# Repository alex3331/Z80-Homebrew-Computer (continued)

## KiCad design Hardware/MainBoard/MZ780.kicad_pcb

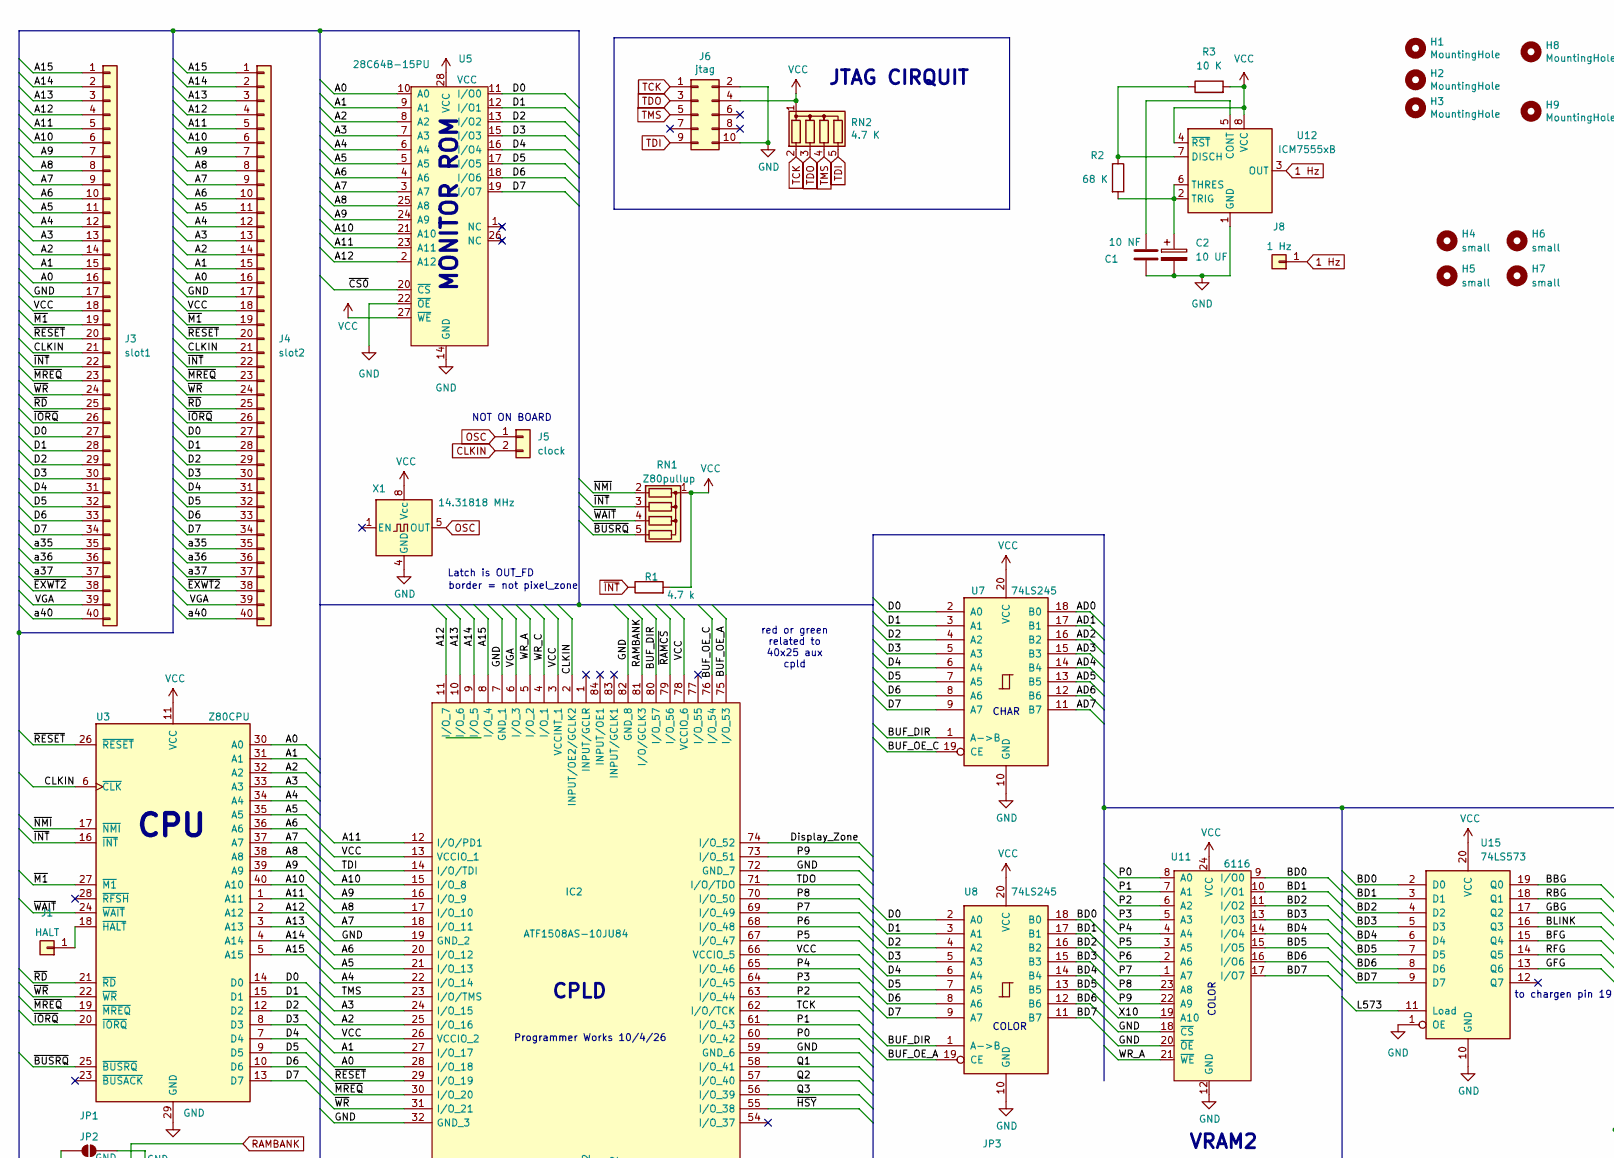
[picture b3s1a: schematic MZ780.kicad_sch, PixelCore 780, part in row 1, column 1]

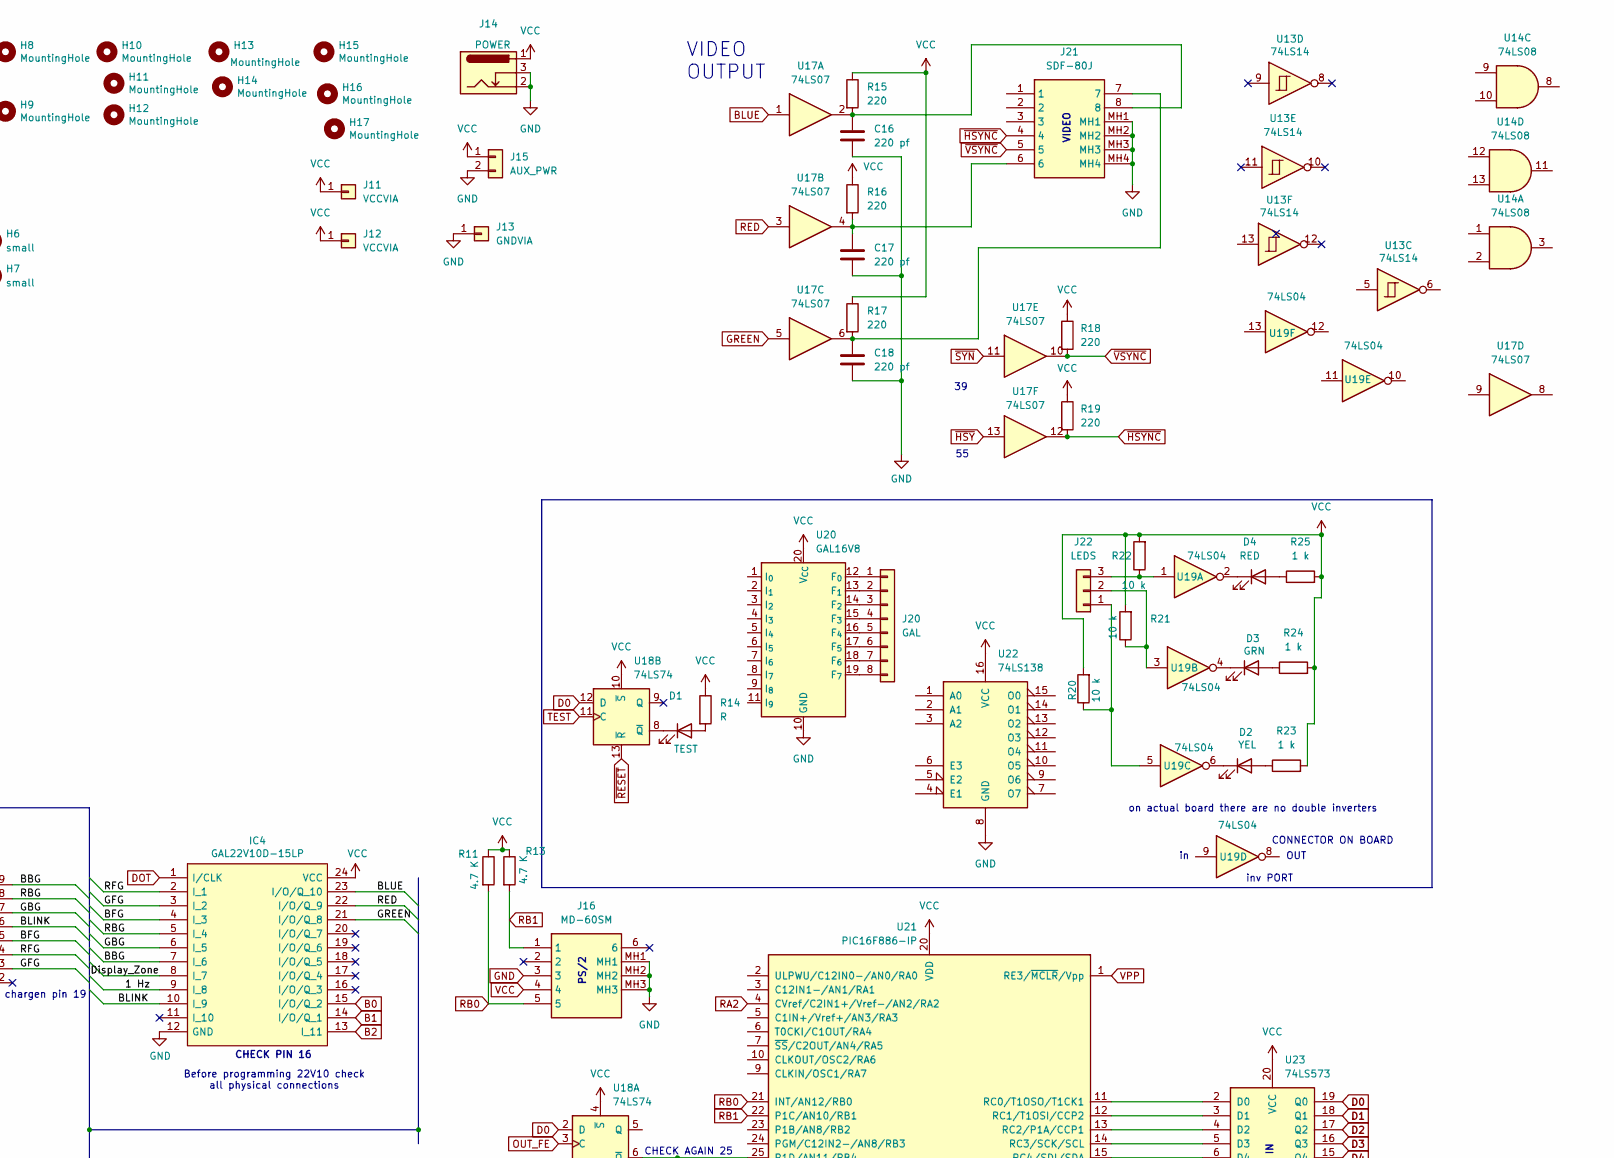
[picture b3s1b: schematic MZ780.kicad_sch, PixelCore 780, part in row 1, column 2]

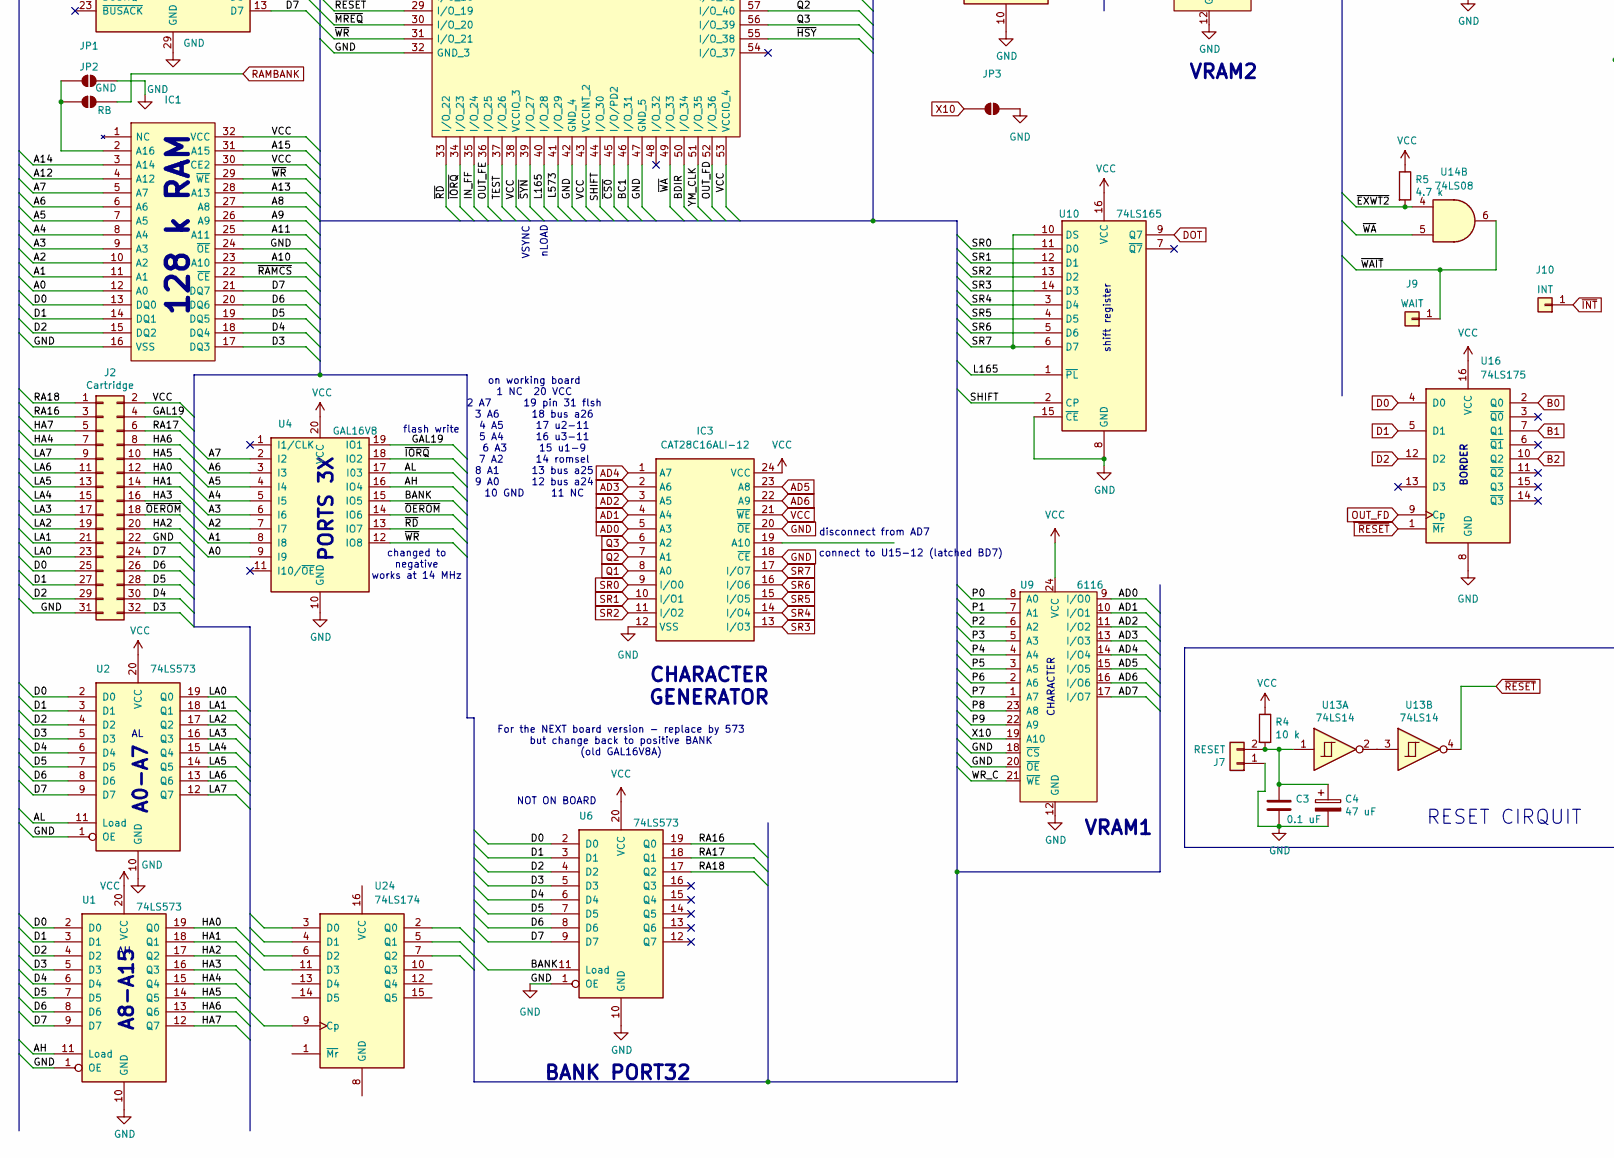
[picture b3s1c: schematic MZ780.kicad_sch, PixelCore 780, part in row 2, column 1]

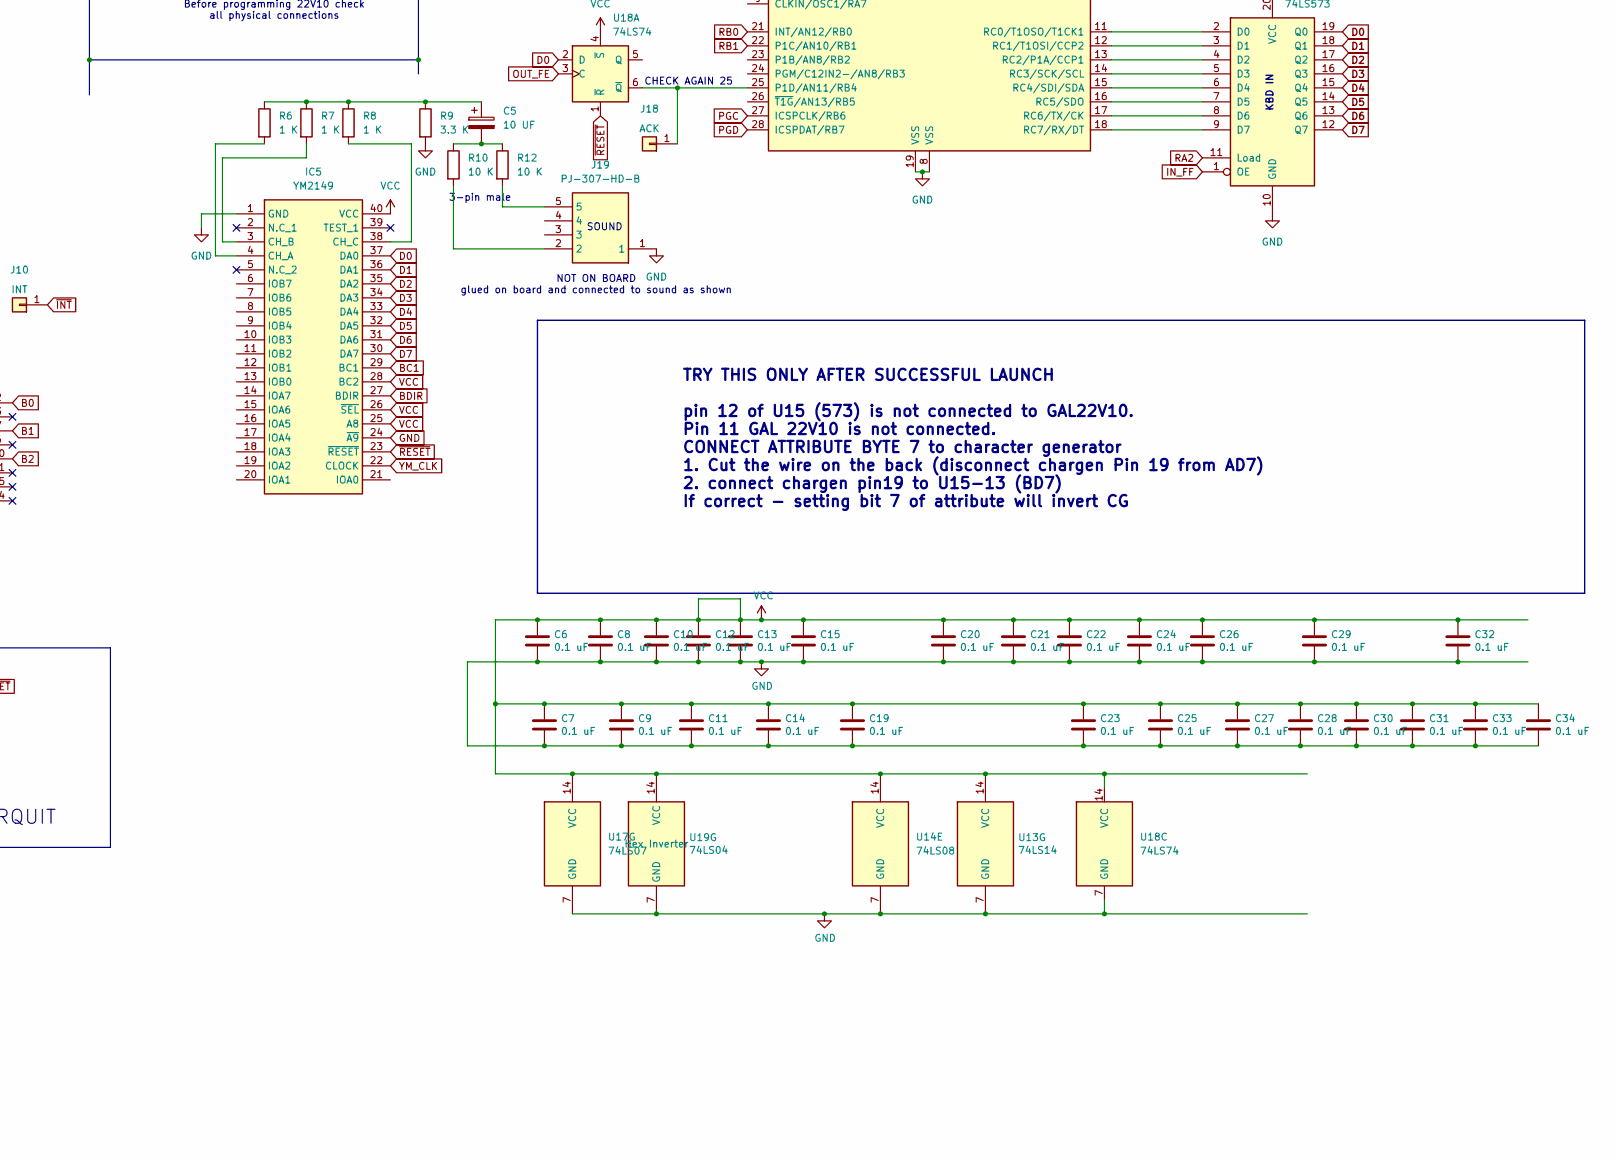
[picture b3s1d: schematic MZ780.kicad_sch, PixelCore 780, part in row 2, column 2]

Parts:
C1: 10 NF; C_Disc_D3.0mm_W1.6mm_P2.50mm
C2, C5: 10 UF; CP_Radial_D5.0mm_P2.50mm
C3, C6, C7, C8, C9, C10, C11, C12, C13, C14, C15, C19, C20, C21, C22, C23, C24, C25, C26, C27, C28, C29, C30, C31, C32, C33, C34: 0.1 uF; C_Disc_D3.0mm_W1.6mm_P2.50mm
C4: 47 uF; CP_Radial_D5.0mm_P2.50mm
C16, C17, C18: 220 pf; C_Disc_D3.0mm_W1.6mm_P2.50mm
D1: TEST; LED_D3.0mm
D2: YEL; LED_D3.0mm
D3: GRN; LED_D3.0mm
D4: RED; LED_D3.0mm
H1, H2, H3, H8, H9, H10, H11, H12, H13, H14, H15, H16, H17: MountingHole; MountingHole_3.2mm_M3_DIN965
H4, H5, H6, H7: small; MountingHole_2.7mm_M2.5_DIN965
IC1: Narrow RAM; DIP-32_W15.24mm; Manufacturer_Part_Number AS6C1008-55PCN; Mouser Part Number 913-AS6C1008-55PCN
IC2: ATF1508AS-10JU84; PLCC-84_THT-Socket; Manufacturer_Part_Number ATF1508AS-10JU84; Mouser Part Number 556-ATF1508AS-10JU84
IC3: CAT28C16ALI-12; DIP-24_W15.24mm; Manufacturer_Part_Number CAT28C16ALI-12
IC4: GAL22V10D-15LP; DIP-24_W7.62mm; Manufacturer_Part_Number GAL22V10D-15LP; Mouser Part Number 842-GAL22V10D15LP
IC5: YM2149; DIP-40_W15.24mm; Manufacturer_Part_Number YM2149
J1: HALT; PinHeader_1x01_P2.54mm_Vertical
J2: Cartridge; PinHeader_2x16_P2.54mm_Vertical
J3: slot1; PinHeader_1x40_P2.54mm_Vertical
J4: slot2; PinHeader_1x40_P2.54mm_Vertical
J5: clock; PinHeader_1x02_P2.54mm_Vertical
J6: jtag; JTAGSOCKET
J7: RESET; PinHeader_1x02_P2.00mm_Vertical
J8: 1 Hz; PinHeader_1x01_P2.54mm_Vertical
J9: WAIT; PinHeader_1x01_P2.54mm_Vertical
J10: INT; PinHeader_1x01_P2.54mm_Vertical
J11, J12: VCCVIA; PinHeader_1x01_P2.54mm_Vertical
J13: GNDVIA; PinHeader_1x01_P2.54mm_Vertical
J14: POWER; BarrelJack_CUI_PJ-102AH_Horizontal
J15: AUX_PWR; PinHeader_1x02_P2.54mm_Vertical
J16: MD-60SM; MD60SM; Manufacturer_Part_Number MD-60SM; Mouser Part Number 490-MD-60SM
J18: ACK; PinHeader_1x01_P2.54mm_Vertical
J19: PJ-307-HD-B; PJ307HDB; Manufacturer_Part_Number PJ-307-HD-B
J20: GAL; PinHeader_1x08_P2.00mm_Vertical
J21: SDF-80J; SDF80J; Manufacturer_Part_Number SDF-80J; Mouser Part Number 490-SDF-80J
J22: LEDS; PinHeader_1x03_P2.54mm_Vertical
JP1, JP3: GND; SolderJumper-2_P1.3mm_Open_RoundedPad1.0x1.5mm
JP2: RB; SolderJumper-2_P1.3mm_Open_RoundedPad1.0x1.5mm
R1, R5: 4.7 k; R_Axial_DIN0204_L3.6mm_D1.6mm_P5.08mm_Horizontal
R2: 68 K; R_Axial_DIN0204_L3.6mm_D1.6mm_P5.08mm_Horizontal
R3, R10, R12: 10 K; R_Axial_DIN0204_L3.6mm_D1.6mm_P5.08mm_Horizontal
R4, R20, R21, R22: 10 k; R_Axial_DIN0204_L3.6mm_D1.6mm_P5.08mm_Horizontal
R6, R7, R8: 1 K; R_Axial_DIN0204_L3.6mm_D1.6mm_P5.08mm_Horizontal
R9: 3.3 K; R_Axial_DIN0204_L3.6mm_D1.6mm_P5.08mm_Horizontal
R11, R13: 4.7 K; R_Axial_DIN0204_L3.6mm_D1.6mm_P5.08mm_Horizontal
R14: R; R_Axial_DIN0204_L3.6mm_D1.6mm_P5.08mm_Horizontal
R15, R16, R17, R18, R19: 220; R_Axial_DIN0204_L3.6mm_D1.6mm_P5.08mm_Horizontal
R23, R24, R25: 1 k; R_Axial_DIN0204_L3.6mm_D1.6mm_P5.08mm_Horizontal
RN1: Z80pullup; R_Array_SIP5
RN2: 4.7 K; R_Array_SIP5
U1, U2, U6, U15, U23: 74LS573; DIP-20_W7.62mm
U3: Z80CPU; DIP-40_W15.24mm
U4, U20: GAL16V8; DIP-20_W7.62mm
U5: 28C64B-15PU; DIP-28_W15.24mm
U7, U8: 74LS245; DIP-20_W7.62mm_Socket
U9, U11: 6116; DIP-24_W7.62mm
U10: 74LS165; DIP-16_W7.62mm
U12: ICM7555xB; DIP-8_W7.62mm
U13: 74LS14; DIP-14_W7.62mm
U14: 74LS08; DIP-14_W7.62mm
U16: 74LS175; DIP-16_W7.62mm
U17: 74LS07; DIP-14_W7.62mm
U18: 74LS74; DIP-14_W7.62mm
U19: 74LS04; DIP-14_W7.62mm
U21: PIC16F886-IP; DIP-28_W7.62mm
U22: 74LS138; DIP-16_W7.62mm
U24: 74LS174; DIP-16_W7.62mm
X1: 14.31818 MHz; Oscillator_DIP-8

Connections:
1 Hz: IC4.9 (I_8), J8.1 (Pin_1_1), U12.3 (OUT)
/A0: IC1.12 (A0), IC2.28 (I/O_18), J3.16, J4.16, U3.30 (A0), U4.9 (I9), U5.10 (A0)
/A1: IC1.11 (A1), IC2.27 (I/O_17), J3.15, J4.15, U3.31 (A1), U4.8 (I8), U5.9 (A1)
/A2: IC1.10 (A2), IC2.25 (I/O_16), J3.14, J4.14, U3.32 (A2), U4.7 (I7), U5.8 (A2)
/A3: IC1.9 (A3), IC2.24 (I/O_15), J3.13, J4.13, U3.33 (A3), U4.6 (I6), U5.7 (A3)
/A4: IC1.8 (A4), IC2.22 (I/O_14), J3.12, J4.12, U3.34 (A4), U4.5 (I5), U5.6 (A4)
/A5: IC1.7 (A5), IC2.21 (I/O_13), J3.11, J4.11, U3.35 (A5), U4.4 (I4), U5.5 (A5)
/A6: IC1.6 (A6), IC2.20 (I/O_12), J3.10, J4.10, U3.36 (A6), U4.3 (I3), U5.4 (A6)
/A7: IC1.5 (A7), IC2.18 (I/O_11), J3.9, J4.9, U3.37 (A7), U4.2 (I2), U5.3 (A7)
/A8: IC1.27 (A8), IC2.17 (I/O_10), J3.8, J4.8, U3.38 (A8), U5.25 (A8)
/A9: IC1.26 (A9), IC2.16 (I/O_9), J3.7, J4.7, U3.39 (A9), U5.24 (A9)
/A10: IC1.23 (A10), IC2.15 (I/O_8), J3.6, J4.6, U3.40 (A10), U5.21 (A10)
/A11: IC1.25 (A11), IC2.12 (I/O/PD1), J3.5, J4.5, U3.1 (A11), U5.23 (A11)
/A12: IC1.4 (A12), IC2.11 (I/O_7), J3.4, J4.4, U3.2 (A12), U5.2 (A12)
/A13: IC1.28 (A13), IC2.10 (I/O_6), J3.3, J4.3, U3.3 (A13)
/A14: IC1.3 (A14), IC2.9 (I/O_5), J3.2, J4.2, U3.4 (A14)
/A15: IC1.31 (A15), IC2.8 (I/O_4), J3.1, J4.1, U3.5 (A15)
/AH: U1.11 (Load), U4.16 (IO4)
/AL: U2.11 (Load), U4.17 (I03)
/BANK: U4.15 (IO5), U6.11 (Load)
/BBG: IC4.7 (I_6), U15.19 (Q0)
/BD0: U8.18 (B0), U11.9 (I/O0), U15.2 (D0)
/BD1: U8.17 (B1), U11.10 (I/O1), U15.3 (D1)
/BD2: U8.16 (B2), U11.11 (I/O2), U15.4 (D2)
/BD3: U8.15 (B3), U11.13 (I/O3), U15.5 (D3)
/BD4: U8.14 (B4), U11.14 (I/O4), U15.6 (D4)
/BD5: U8.13 (B5), U11.15 (I/O5), U15.7 (D5)
/BD6: U8.12 (B6), U11.16 (I/O6), U15.8 (D6)
/BD7: U8.11 (B7), U11.17 (I/O7), U15.9 (D7)
/BFG: IC4.4 (I_3), U15.15 (Q4)
/BLINK: IC4.10 (I_9), U15.16 (Q3)
/BUF_DIR: IC2.80 (I/O_57), U7.1 (A->B), U8.1 (A->B)
/BUF_OE_A: IC2.75 (I/O_53), U8.19 (CE)
/BUF_OE_C: IC2.76 (I/O_54), U7.19 (CE)
/Display_Zone: IC2.74 (I/O_52), IC4.8 (I_7)
/GAL19: J2.4, U4.19 (IO1)
/GBG: IC4.6 (I_5), U15.17 (Q2)
/GFG: IC4.3 (I_2), U15.13 (Q6)
/HA0: J2.12, U1.19 (Q0)
/HA1: J2.14, U1.18 (Q1)
/HA2: J2.20, U1.17 (Q2)
/HA3: J2.16, U1.16 (Q3)
/HA4: J2.7, U1.15 (Q4)
/HA5: J2.10, U1.14 (Q5)
/HA6: J2.8, U1.13 (Q6)
/HA7: J2.5, U1.12 (Q7)
/INVERT: U15.12 (Q7)
/L165: IC2.40 (I/O_28), U10.1 (~PL)
/L573: IC2.41 (I/O_29), U15.11 (Load)
/LA0: J2.23, U2.19 (Q0)
/LA1: J2.21, U2.18 (Q1)
/LA2: J2.19, U2.17 (Q2)
/LA3: J2.17, U2.16 (Q3)
/LA4: J2.15, U2.15 (Q4)
/LA5: J2.13, U2.14 (Q5)
/LA6: J2.11, U2.13 (Q6)
/LA7: J2.9, U2.12 (Q7)
/P0: IC2.60 (I/O_42), U9.8 (A0), U11.8 (A0)
/P1: IC2.61 (I/O_43), U9.7 (A1), U11.7 (A1)
/P2: IC2.63 (I/O_44), U9.6 (A2), U11.6 (A2)
/P3: IC2.64 (I/O_45), U9.5 (A3), U11.5 (A3)
/P4: IC2.65 (I/O_46), U9.4 (A4), U11.4 (A4)
/P5: IC2.67 (I/O_47), U9.3 (A5), U11.3 (A5)
/P6: IC2.68 (I/O_48), U9.2 (A6), U11.2 (A6)
/P7: IC2.69 (I/O_49), U9.1 (A7), U11.1 (A7)
/P8: IC2.70 (I/O_50), U9.23 (A8), U11.23 (A8)
/P9: IC2.73 (I/O_51), U9.22 (A9), U11.22 (A9)
/RA16: J2.3, U6.19 (Q0)
/RA17: J2.6, U6.18 (Q1)
/RA18: J2.1, U6.17 (Q2)
/RBG: IC4.5 (I_4), U15.18 (Q1)
/RFG: IC4.2 (I_1), U15.14 (Q5)
/SHIFT: IC2.44 (I/O_30), U10.2 (CP)
/VGA: IC2.6 (I/O_3), J3.39, J4.39
/WR_A: IC2.5 (I/O_2), U11.21 (~WE)
/WR_C: IC2.4 (I/O_1), U9.21 (~WE)
/a35: J3.35, J4.35
/a36: J3.36, J4.36
/a37: J3.37, J4.37
/a40: J3.40, J4.40
/~BUSRQ: RN1.5 (R4), U3.25 (~BUSRQ)
/~CS0: IC2.45 (I/O/PD2), U5.20 (~CS)
/~EXWT2: J3.38, J4.38, R5.2, U14.4
/~IORQ: IC2.34 (I/O_23), J3.26, J4.26, U3.20 (~IORQ), U4.18 (IO2)
/~M1: J3.19, J4.19, U3.27 (~M1)
/~MREQ: IC2.30 (I/O_20), J3.23, J4.23, U3.19 (~MREQ)
/~NMI: RN1.2 (R1), U3.17 (~NMI)
/~OEROM: J2.18, U4.14 (IO6)
/~RAMCS: IC1.22 (~CE), IC2.79 (I/O_56)
/~RD: IC2.33 (I/O_22), J3.25, J4.25, U3.21 (~RD), U4.13 (IO7)
/~WAIT: J9.1 (Pin_1_1), RN1.4 (R3), U3.24 (~WAIT), U14.6
/~WA: IC2.49 (I/O_33), U14.5
/~WR: IC1.29 (~WE), IC2.31 (I/O_21), J3.24, J4.24, U3.22 (~WR), U4.12 (IO8)
AD0: IC3.5 (A3), U7.18 (B0), U9.9 (I/O0)
AD1: IC3.4 (A4), U7.17 (B1), U9.10 (I/O1)
AD2: IC3.3 (A5), U7.16 (B2), U9.11 (I/O2)
AD3: IC3.2 (A6), U7.15 (B3), U9.13 (I/O3)
AD4: IC3.1 (A7), U7.14 (B4), U9.14 (I/O4)
AD5: IC3.23 (A8), U7.13 (B5), U9.15 (I/O5)
AD6: IC3.22 (A9), U7.12 (B6), U9.16 (I/O6)
AD7: IC3.19 (A10), U7.11 (B7), U9.17 (I/O7)
B0: IC4.15 (I/O/Q_2), U16.2 (Q0)
B1: IC4.14 (I/O/Q_1), U16.7 (Q1)
B2: IC4.13 (I_11), U16.10 (Q2)
BC1: IC2.46 (I/O_31), IC5.29 (BC1)
BDIR: IC2.50 (I/O_34), IC5.27 (BDIR)
BLUE: IC4.23 (I/O/Q_10), U17.1
CLKIN: IC2.2 (INPUT/OE2/GCLK2), J3.21, J4.21, J5.2, U3.6 (~CLK)
D0: IC1.13 (DQ0), IC5.37 (DA0), J2.25, J3.27, J4.27, U1.2 (D0), U2.2 (D0), U3.14 (D0), U5.11 (I/O0), U6.2 (D0), U7.2 (A0), U8.2 (A0), U16.4 (D0), U18.2 (D), U18.12 (D), U23.19 (Q0)
D1: IC1.14 (DQ1), IC5.36 (DA1), J2.27, J3.28, J4.28, U1.3 (D1), U2.3 (D1), U3.15 (D1), U5.12 (I/O1), U6.3 (D1), U7.3 (A1), U8.3 (A1), U16.5 (D1), U23.18 (Q1)
D2: IC1.15 (DQ2), IC5.35 (DA2), J2.29, J3.29, J4.29, U1.4 (D2), U2.4 (D2), U3.12 (D2), U5.13 (I/O2), U6.4 (D2), U7.4 (A2), U8.4 (A2), U16.12 (D2), U23.17 (Q2)
D3: IC1.17 (DQ3), IC5.34 (DA3), J2.32, J3.30, J4.30, U1.5 (D3), U2.5 (D3), U3.8 (D3), U5.15 (I/O3), U6.5 (D3), U7.5 (A3), U8.5 (A3), U23.16 (Q3)
D4: IC1.18 (DQ4), IC5.33 (DA4), J2.30, J3.31, J4.31, U1.6 (D4), U2.6 (D4), U3.7 (D4), U5.16 (I/O4), U6.6 (D4), U7.6 (A4), U8.6 (A4), U23.15 (Q4)
D5: IC1.19 (DQ5), IC5.32 (DA5), J2.28, J3.32, J4.32, U1.7 (D5), U2.7 (D5), U3.9 (D5), U5.17 (I/O5), U6.7 (D5), U7.7 (A5), U8.7 (A5), U23.14 (Q5)
D6: IC1.20 (DQ6), IC5.31 (DA6), J2.26, J3.33, J4.33, U1.8 (D6), U2.8 (D6), U3.10 (D6), U5.18 (I/O6), U6.8 (D6), U7.8 (A6), U8.8 (A6), U23.13 (Q6)
D7: IC1.21 (DQ7), IC5.30 (DA7), J2.24, J3.34, J4.34, U1.9 (D7), U2.9 (D7), U3.13 (D7), U5.19 (I/O7), U6.9 (D7), U7.9 (A7), U8.9 (A7), U23.12 (Q7)
DOT: IC4.1 (I/CLK), U10.9 (Q7)
GND: C1.2, C2.2, C3.2, C4.2, C6.2, C7.2, C8.2, C9.2, C10.2, C11.2, C12.2, C13.2, C14.2, C15.2, C16.2, C17.2, C18.2, C19.2, C20.2, C21.2, C22.2, C23.2, C24.2, C25.2, C26.2, C27.2, C28.2, C29.2, C30.2, C31.2, C32.2, C33.2, C34.2, IC1.16 (VSS), IC1.24 (~OE), IC2.7 (GND_1), IC2.19 (GND_2), IC2.32 (GND_3), IC2.42 (GND_4), IC2.47 (GND_5), IC2.59 (GND_6), IC2.72 (GND_7), IC2.82 (GND_8), IC3.12 (VSS), IC3.18 (~CE), IC3.20 (~OE), IC4.12 (GND), IC5.1 (GND), IC5.24 (~A9), J2.22, J2.31, J3.17, J4.17, J6.2, J6.10, J7.1, J13.1 (Pin_1_1), J14.2, J14.3, J15.2, J16.3, J16.MH1, J16.MH2, J16.MH3, J19.1, J21.MH1, J21.MH2, J21.MH3, J21.MH4, JP1.2 (B), JP3.2 (B), R9.2, U1.1 (OE), U1.10 (GND), U2.1 (OE), U2.10 (GND), U3.29 (GND), U4.10 (GND), U5.14 (GND), U5.22 (~OE), U6.1 (OE), U6.10 (GND), U7.10 (GND), U8.10 (GND), U9.12 (GND), U9.18 (~CS), U9.20 (~OE), U10.8 (GND), U10.15 (~CE), U11.12 (GND), U11.18 (~CS), U11.20 (~OE), U12.1 (GND), U13.7 (GND), U14.7 (GND), U15.1 (OE), U15.10 (GND), U16.8 (GND), U17.7 (GND), U18.7 (GND), U19.7 (GND), U20.10 (GND), U21.8 (VSS), U21.19 (VSS), U22.8 (GND), U23.10 (GND), X1.4 (GND); also elsewhere on the board
GREEN: IC4.21 (I/O/Q_8), U17.5
IN_FF: IC2.35 (I/O_24), U23.1 (OE)
unnamed: C5.1, R6.1, R7.1, R8.1, R9.1
unnamed: C5.2, R10.1, R12.1
unnamed: C16.1, J21.8, R15.2, U17.2
unnamed: C17.1, J21.6, R16.2, U17.4
unnamed: C18.1, J21.7, R17.2, U17.6
unnamed: D1.2 (A), R14.2
unnamed: D1.1 (K), U18.8 (~Q)
unnamed: D2.2 (A), R23.1
unnamed: D3.2 (A), R24.1
unnamed: D4.2 (A), R25.1
unnamed: IC1.2 (A16), JP1.1 (A), JP2.1 (A)
unnamed: IC5.4 (CH_A), R6.2
unnamed: IC5.3 (CH_B), R7.2
unnamed: IC5.38 (CH_C), R8.2
unnamed: J1.1 (Pin_1_1), U3.18 (~HALT)
unnamed: C3.1, C4.1, J7.2, R4.2, U13.1
unnamed: J18.1 (Pin_1_1), U18.6 (~Q), U21.25 (P1D/AN11/RB4)
unnamed: J19.2, R10.2
unnamed: J19.5, R12.2
unnamed: J20.1, U20.12 (F_{0})
unnamed: J20.2, U20.13 (F_{1})
unnamed: J20.3, U20.14 (F_{2})
unnamed: J20.4, U20.15 (F_{3})
unnamed: J20.5, U20.16 (F_{4})
unnamed: J20.6, U20.17 (F_{5})
unnamed: J20.7, U20.18 (F_{6})
unnamed: J20.8, U20.19 (F_{7})
unnamed: J22.3, R22.1, U19.1
unnamed: C1.1, U12.5 (CONT)
unnamed: R2.1, R3.1, U12.7 (DISCH)
unnamed: C2.1, R2.2, U12.2 (TRIG), U12.6 (THRES)
unnamed: U13.2, U13.3
unnamed: U19.11, U19.12
unnamed: U21.11 (RC0/T1OSO/T1CK1), U23.2 (D0)
unnamed: U21.12 (RC1/T1OSI/CCP2), U23.3 (D1)
unnamed: U21.13 (RC2/P1A/CCP1), U23.4 (D2)
unnamed: U21.14 (RC3/SCK/SCL), U23.5 (D3)
unnamed: U21.15 (RC4/SDI/SDA), U23.6 (D4)
unnamed: U21.16 (RC5/SDO), U23.7 (D5)
unnamed: U21.17 (RC6/TX/CK), U23.8 (D6)
unnamed: U21.18 (RC7/RX/DT), U23.9 (D7)
OSC: J5.1, X1.5 (OUT)
OUT_FD: IC2.52 (I/O_36), U16.9 (Cp)
OUT_FE: IC2.36 (I/O_25), U18.3 (C)
PGC: U21.27 (ICSPCLK/RB6)
PGD: U21.28 (ICSPDAT/RB7)
Q1: IC2.58 (I/O_41), IC3.8 (A0)
Q2: IC2.57 (I/O_40), IC3.7 (A1)
Q3: IC2.56 (I/O_39), IC3.6 (A2)
RA2: U21.4 (CVref/C2IN1+/Vref-/AN2/RA2), U23.11 (Load)
RAMBANK: IC2.81 (I/O/GCLK3), JP2.2 (B)
RB0: J16.5, R11.2, U21.21 (INT/AN12/RB0)
RB1: J16.1, R13.2, U21.22 (P1C/AN10/RB1)
RED: IC4.22 (I/O/Q_9), U17.3
SR0: IC3.9 (I/O0), U10.11 (D0)
SR1: IC3.10 (I/O1), U10.12 (D1)
SR2: IC3.11 (I/O2), U10.13 (D2)
SR3: IC3.13 (I/O3), U10.14 (D3)
SR4: IC3.14 (I/O4), U10.3 (D4)
SR5: IC3.15 (I/O5), U10.4 (D5)
SR6: IC3.16 (I/O6), U10.5 (D6)
SR7: IC3.17 (I/O7), U10.6 (D7), U10.10 (DS)
TCK: IC2.62 (I/O/TCK), J6.1, RN2.2 (R1)
TDI: IC2.14 (I/O/TDI), J6.9, RN2.5 (R4)
TDO: IC2.71 (I/O/TDO), J6.3, RN2.3 (R2)
TEST: IC2.37 (I/O_26), U18.11 (C)
TMS: IC2.23 (I/O/TMS), J6.5, RN2.4 (R3)
VCC: C6.1, C7.1, C8.1, C9.1, C10.1, C11.1, C12.1, C13.1, C14.1, C15.1, C19.1, C20.1, C21.1, C22.1, C23.1, C24.1, C25.1, C26.1, C27.1, C28.1, C29.1, C30.1, C31.1, C32.1, C33.1, C34.1, IC1.30 (CE2), IC1.32 (VCC), IC2.3 (VCCINT_1), IC2.13 (VCCIO_1), IC2.26 (VCCIO_2), IC2.38 (VCCIO_3), IC2.43 (VCCINT_2), IC2.53 (VCCIO_4), IC2.66 (VCCIO_5), IC2.78 (VCCIO_6), IC3.21 (~WE), IC3.24 (VCC), IC4.24 (VCC), IC5.25 (A8), IC5.26 (~SEL), IC5.28 (BC2), IC5.40 (VCC), J2.2, J3.18, J4.18, J6.4, J11.1 (Pin_1_1), J12.1 (Pin_1_1), J14.1, J15.1, J16.4, R1.2, R3.2, R4.1, R5.1, R11.1, R13.1, R14.1, R15.1, R16.1, R17.1, R18.1, R19.1, R20.2, R21.2, R22.2, R23.2, R24.2, R25.2, RN1.1 (common), RN2.1 (common), U1.20 (VCC), U2.20 (VCC), U3.11 (VCC), U4.20 (VCC), U5.27 (~WE), U5.28 (VCC), U6.20 (VCC), U7.20 (VCC), U8.20 (VCC), U9.24 (VCC), U10.16 (VCC), U11.24 (VCC), U12.4 (~RST), U12.8 (VCC), U13.14 (VCC), U14.14 (VCC), U15.20 (VCC), U16.16 (VCC), U17.14 (VCC), U18.4 (~S), U18.10 (~S), U18.14 (VCC), U19.14 (VCC), U20.20 (V_{CC}), U21.20 (VDD), U22.16 (VCC), U23.20 (VCC), X1.8 (Vcc); also elsewhere on the board
VPP: U21.1 (RE3/~MCLR/Vpp)
X10: JP3.1 (A), U9.19 (A10), U11.19 (A10)
YM_CLK: IC2.51 (I/O_35), IC5.22 (CLOCK)
~HSYNC: J21.4, R19.2, U17.12
~HSY: IC2.55 (I/O_38), U17.13
~INT: J3.22, J4.22, J10.1 (Pin_1_1), R1.1, RN1.3 (R2), U3.16 (~INT)
~RESET: IC2.29 (I/O_19), IC5.23 (~RESET), J3.20, J4.20, U3.26 (~RESET), U13.4, U16.1 (~Mr), U18.1 (~R), U18.13 (~R)
~SYN: IC2.39 (I/O_27), U17.11
~VSYNC: J21.5, R18.2, U17.10

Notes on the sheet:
inv PORT
connect to U15-12 (latched BD7)
Programmer Works 10/4/26
VSYNC
border = not pixel_zone
PORTS 3X
VRAM1
nLOAD
COLOR
BORDER
CPU
JTAG CIRQUIT
KBD IN
on actual board there are no double inverters
flash write
CPLD
VIDEO
NOT ON BOARD
3-pin male
TRY THIS ONLY AFTER SUCCESSFUL LAUNCH pin 12 of U15 (573) is not connected to GAL22V10. Pin 11 GAL 22V10 is not connected. CONNECT ATTRIBUTE BYTE 7 to character generator 1. Cut the wire on the back (disconnect chargen Pin 19 from AD7) 2. connect chargen pin19 to U15-13 (BD7) If correct - setting b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
disconnect from AD7
Latch is OUT_FD
A8-A15
CONNECTOR ON BOARD
red or green related to 40x25 aux cpld
on working board 1 NC 20 VCC 2 A7 19 pin 31 flsh 3 A6 18 bus a26 4 A5 17 u2-11 5 A4 16 u3-11 6 A3 15 u1-9 7 A2 14 romsel 8 A1 13 bus a25 9 A0 12 bus a24 10 GND 11 NC
128 k RAM
shift register
to chargen pin 19
VRAM2
SOUND
VIDEO OUTPUT
CHARACTER
BANK PORT32
PS/2
MONITOR ROM
CHAR
CHECK PIN 16
A0-A7
NOT ON BOARD glued on board and connected to sound as shown

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
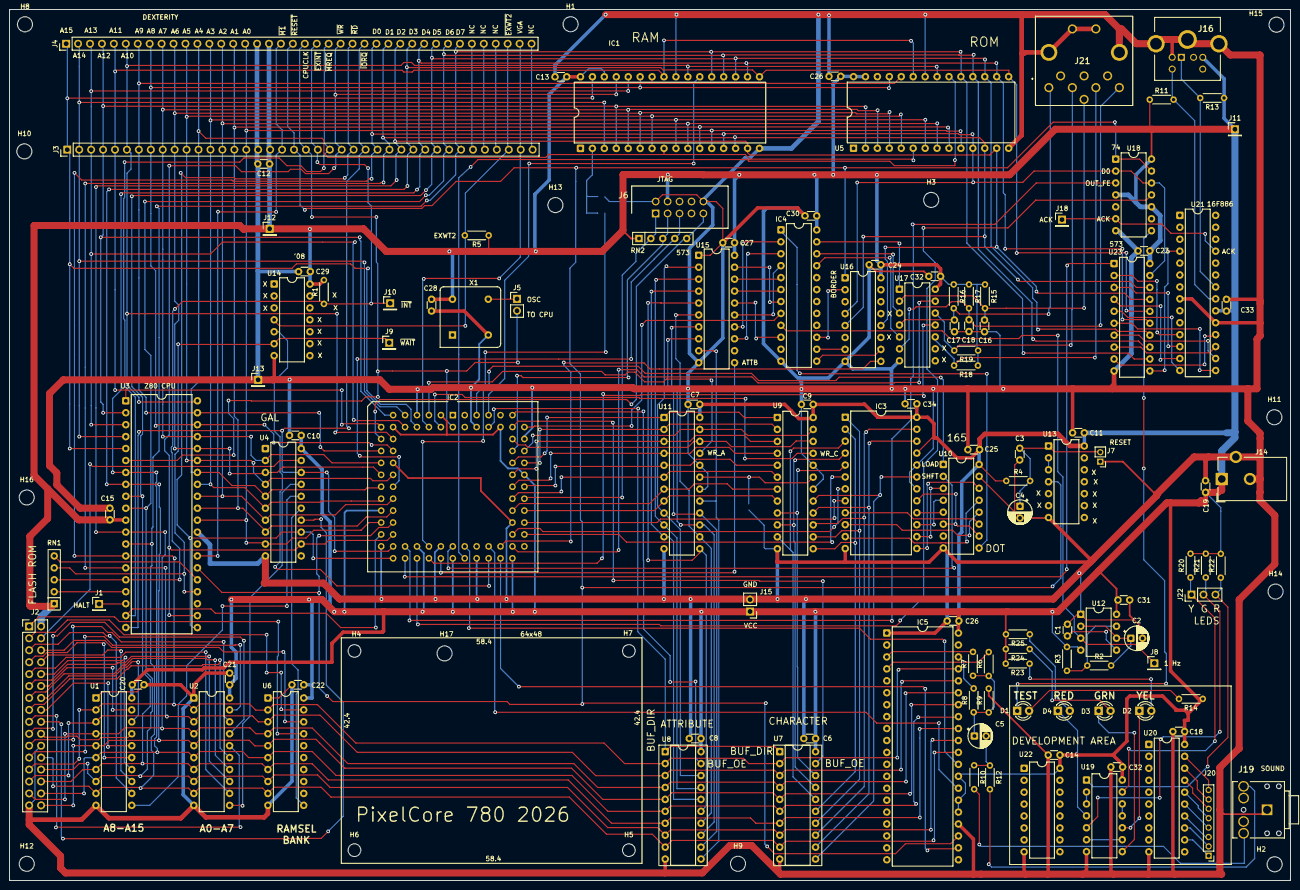
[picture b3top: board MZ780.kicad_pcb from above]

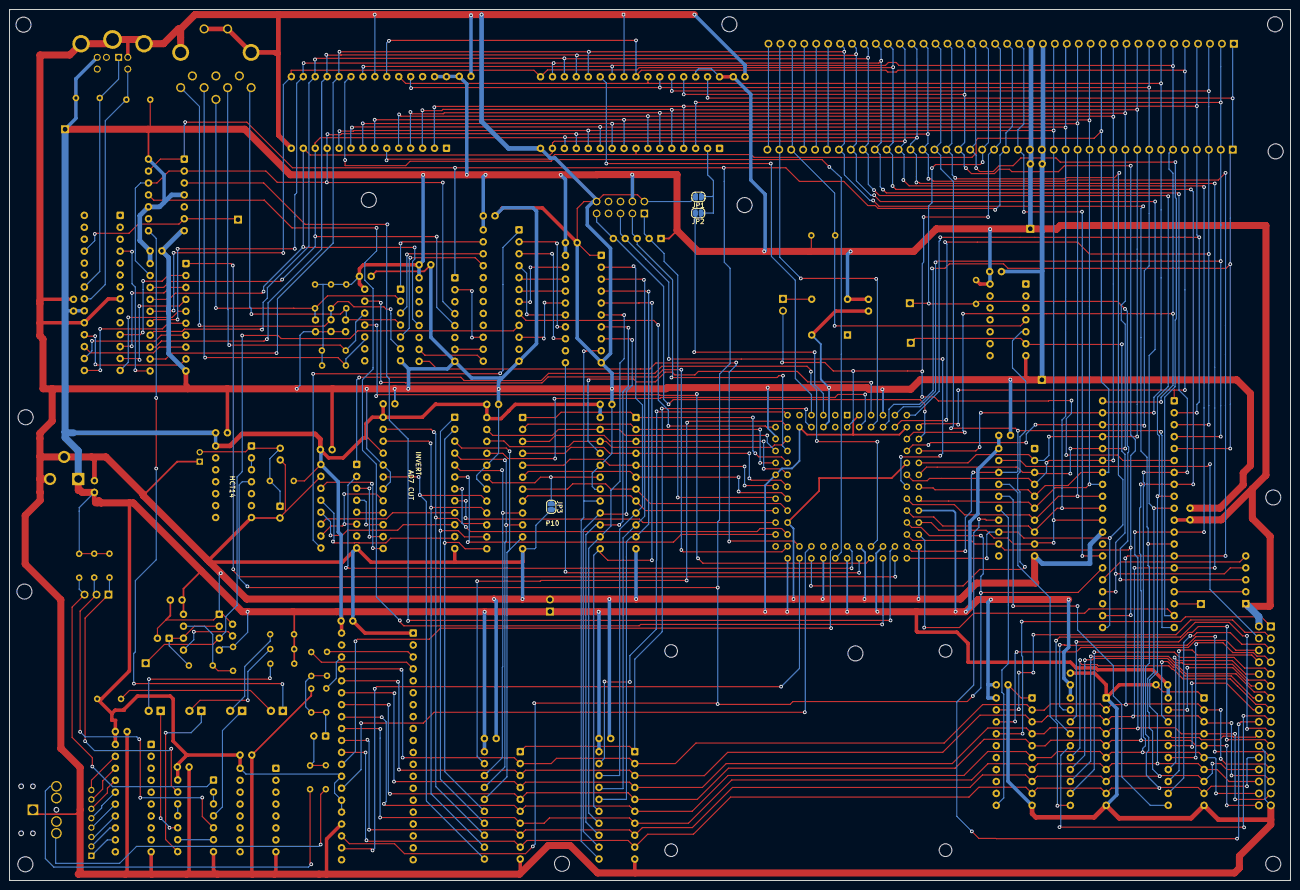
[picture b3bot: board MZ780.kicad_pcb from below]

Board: 2 copper layers, 272.6 x 185.4 mm, 138 parts (3 on the bottom side), 200 nets.

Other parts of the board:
C18#2, C26#2, C32#2: 0.1 uF; C_Disc_D3.0mm_W1.6mm_P2.50mm

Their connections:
GND: C18#2.2, C26#2.2, C32#2.2; also elsewhere on the board
VCC: C18#2.1, C26#2.1, C32#2.1; also elsewhere on the board

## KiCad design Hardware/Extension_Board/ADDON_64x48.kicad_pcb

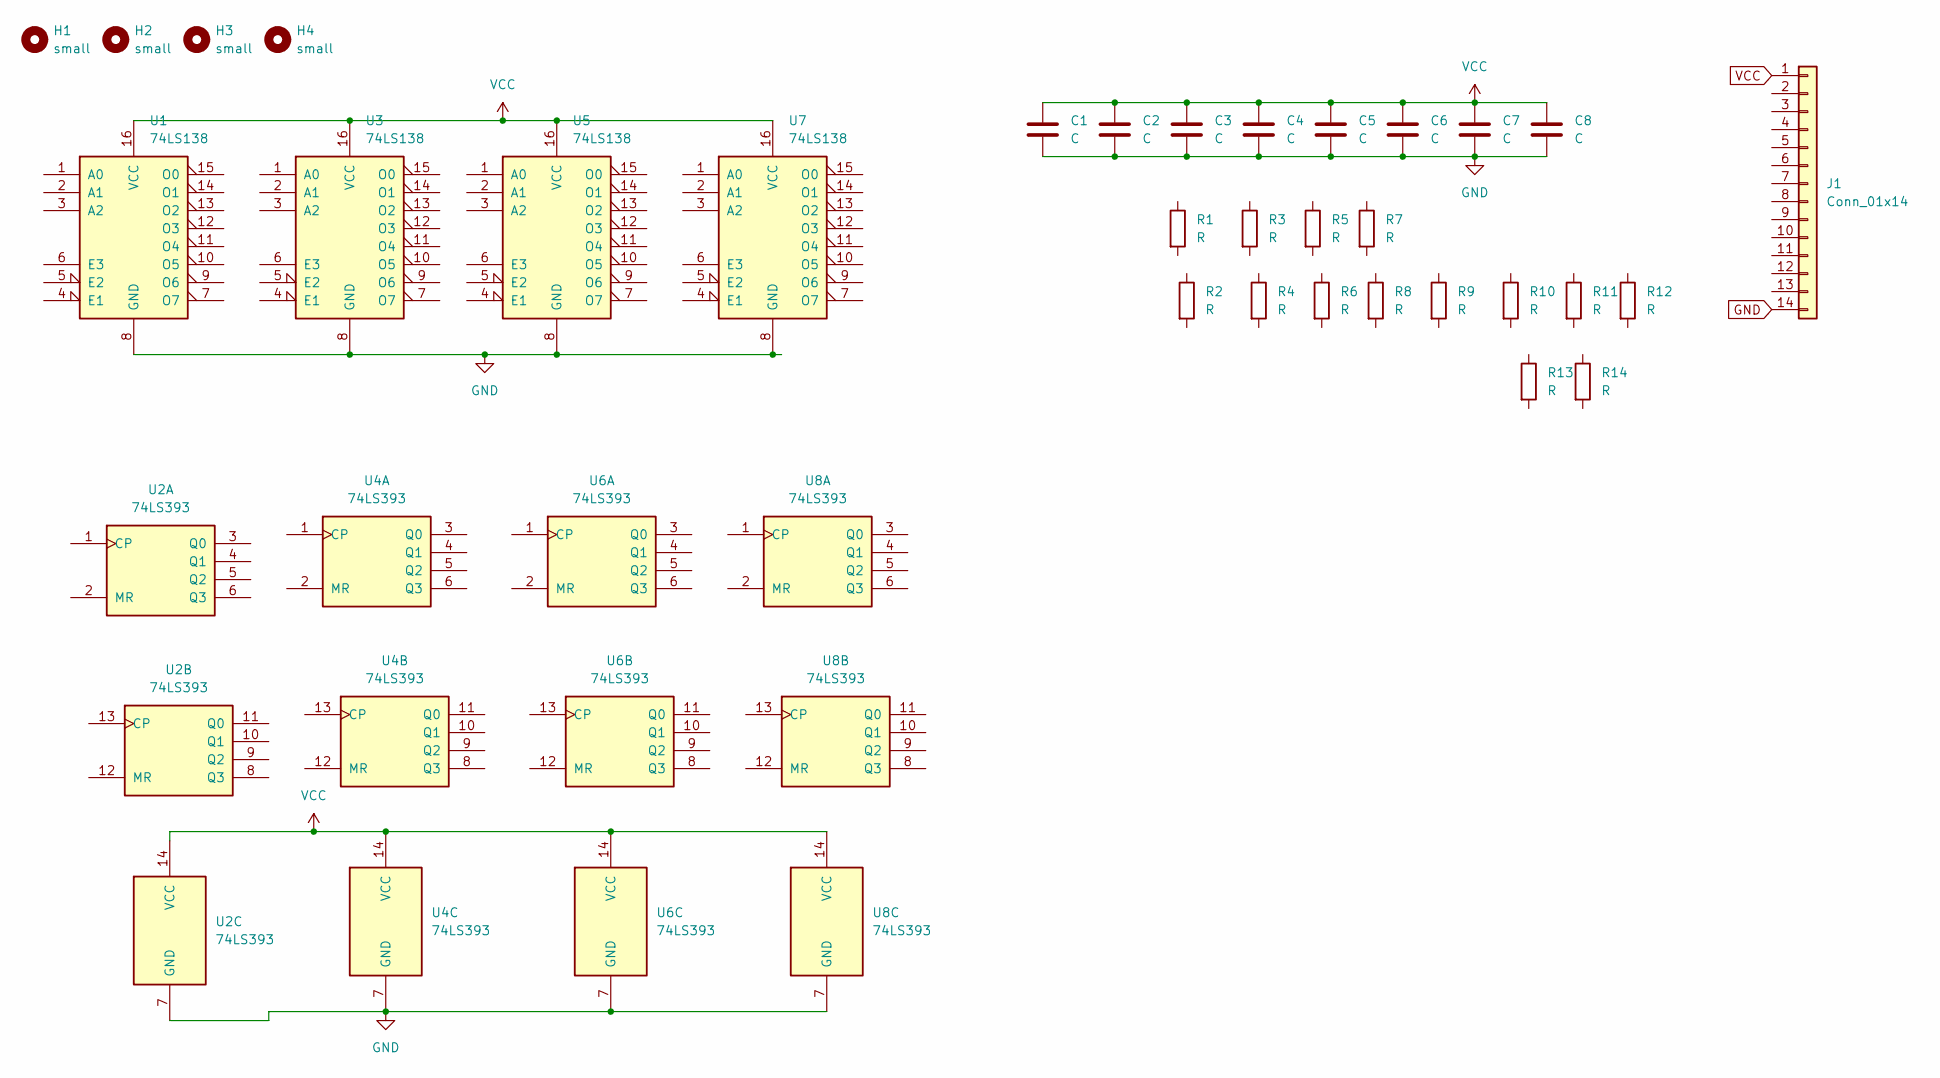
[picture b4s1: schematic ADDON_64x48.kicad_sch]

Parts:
C1, C2, C3, C4, C5, C6, C7, C8: C; C_Disc_D3.0mm_W1.6mm_P2.50mm
H1, H2, H3, H4: small; MountingHole_2.7mm_M2.5_DIN965
J1: Conn_01x14; PinHeader_1x14_P2.54mm_Vertical
R1, R2, R3, R4, R5, R6, R7, R8, R9, R10, R11, R12, R13, R14: R; R_Axial_DIN0204_L3.6mm_D1.6mm_P5.08mm_Vertical
U1, U3, U5, U7: 74LS138; DIP-16_W7.62mm
U2, U4, U6, U8: 74LS393; DIP-14_W7.62mm

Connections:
GND: C1.2, C2.2, C3.2, C4.2, C5.2, C6.2, C7.2, C8.2, J1.14, U1.8 (GND), U2.7 (GND), U3.8 (GND), U4.7 (GND), U5.8 (GND), U6.7 (GND), U7.8 (GND), U8.7 (GND)
VCC: C1.1, C2.1, C3.1, C4.1, C5.1, C6.1, C7.1, C8.1, J1.1, U1.16 (VCC), U2.14 (VCC), U3.16 (VCC), U4.14 (VCC), U5.16 (VCC), U6.14 (VCC), U7.16 (VCC), U8.14 (VCC)

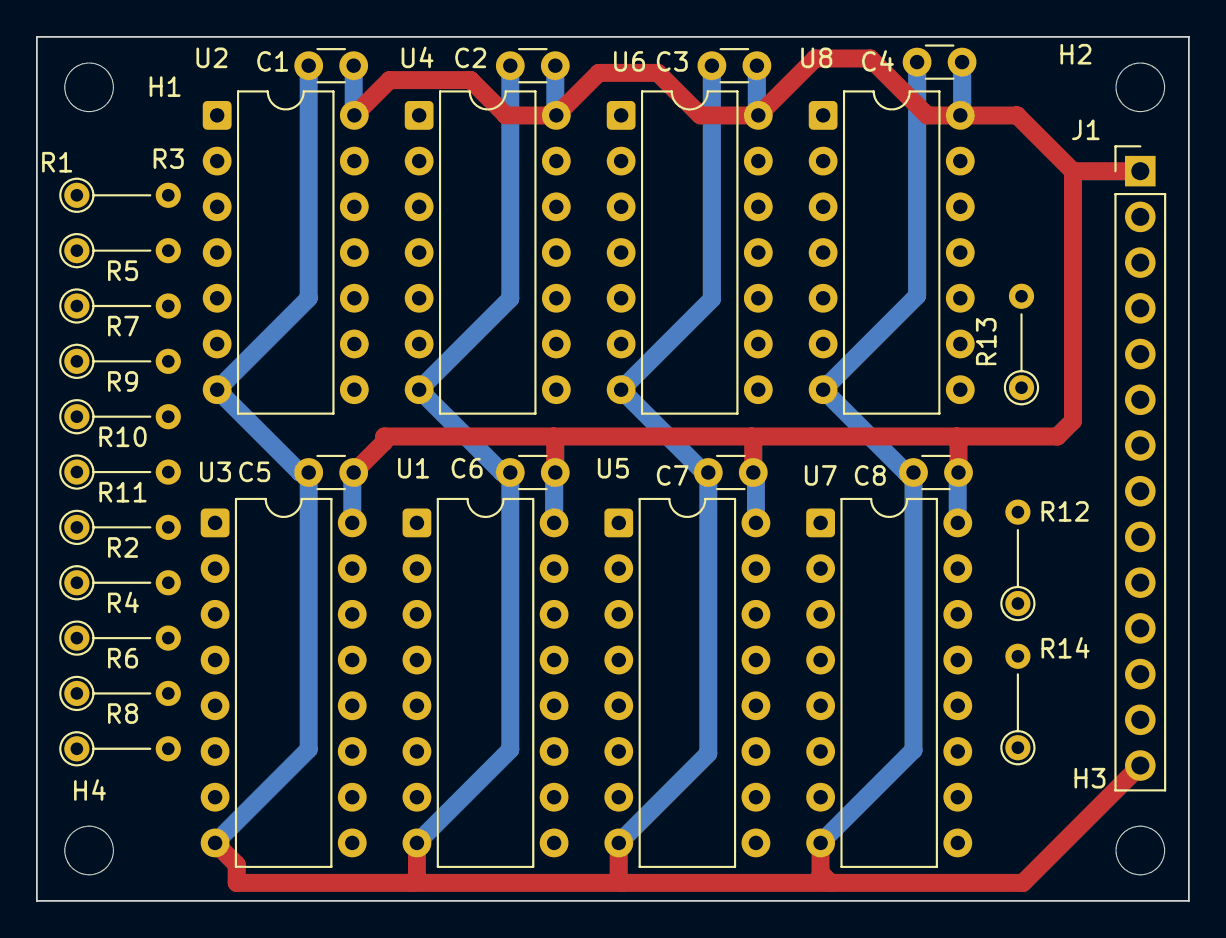
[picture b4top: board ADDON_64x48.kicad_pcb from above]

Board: 2 copper layers, 64.0 x 48.0 mm, 35 parts (0 on the bottom side), 2 nets.
